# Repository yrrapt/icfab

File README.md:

# ICFab

Currently only includes a DMD based lithography protoype design.

The design has been created for use with the ZTurn Zynq development board for driving the information to the DMD chip.

The design is created in KiCad.
The BOM can be found here: [BOM](https://htmlpreview.github.io/?https://github.com/yrrapt/icfab/blob/master/Design/Projector/DLP_Board/dlp_01/dlp_01_sch_brd/bom/ibom.html)

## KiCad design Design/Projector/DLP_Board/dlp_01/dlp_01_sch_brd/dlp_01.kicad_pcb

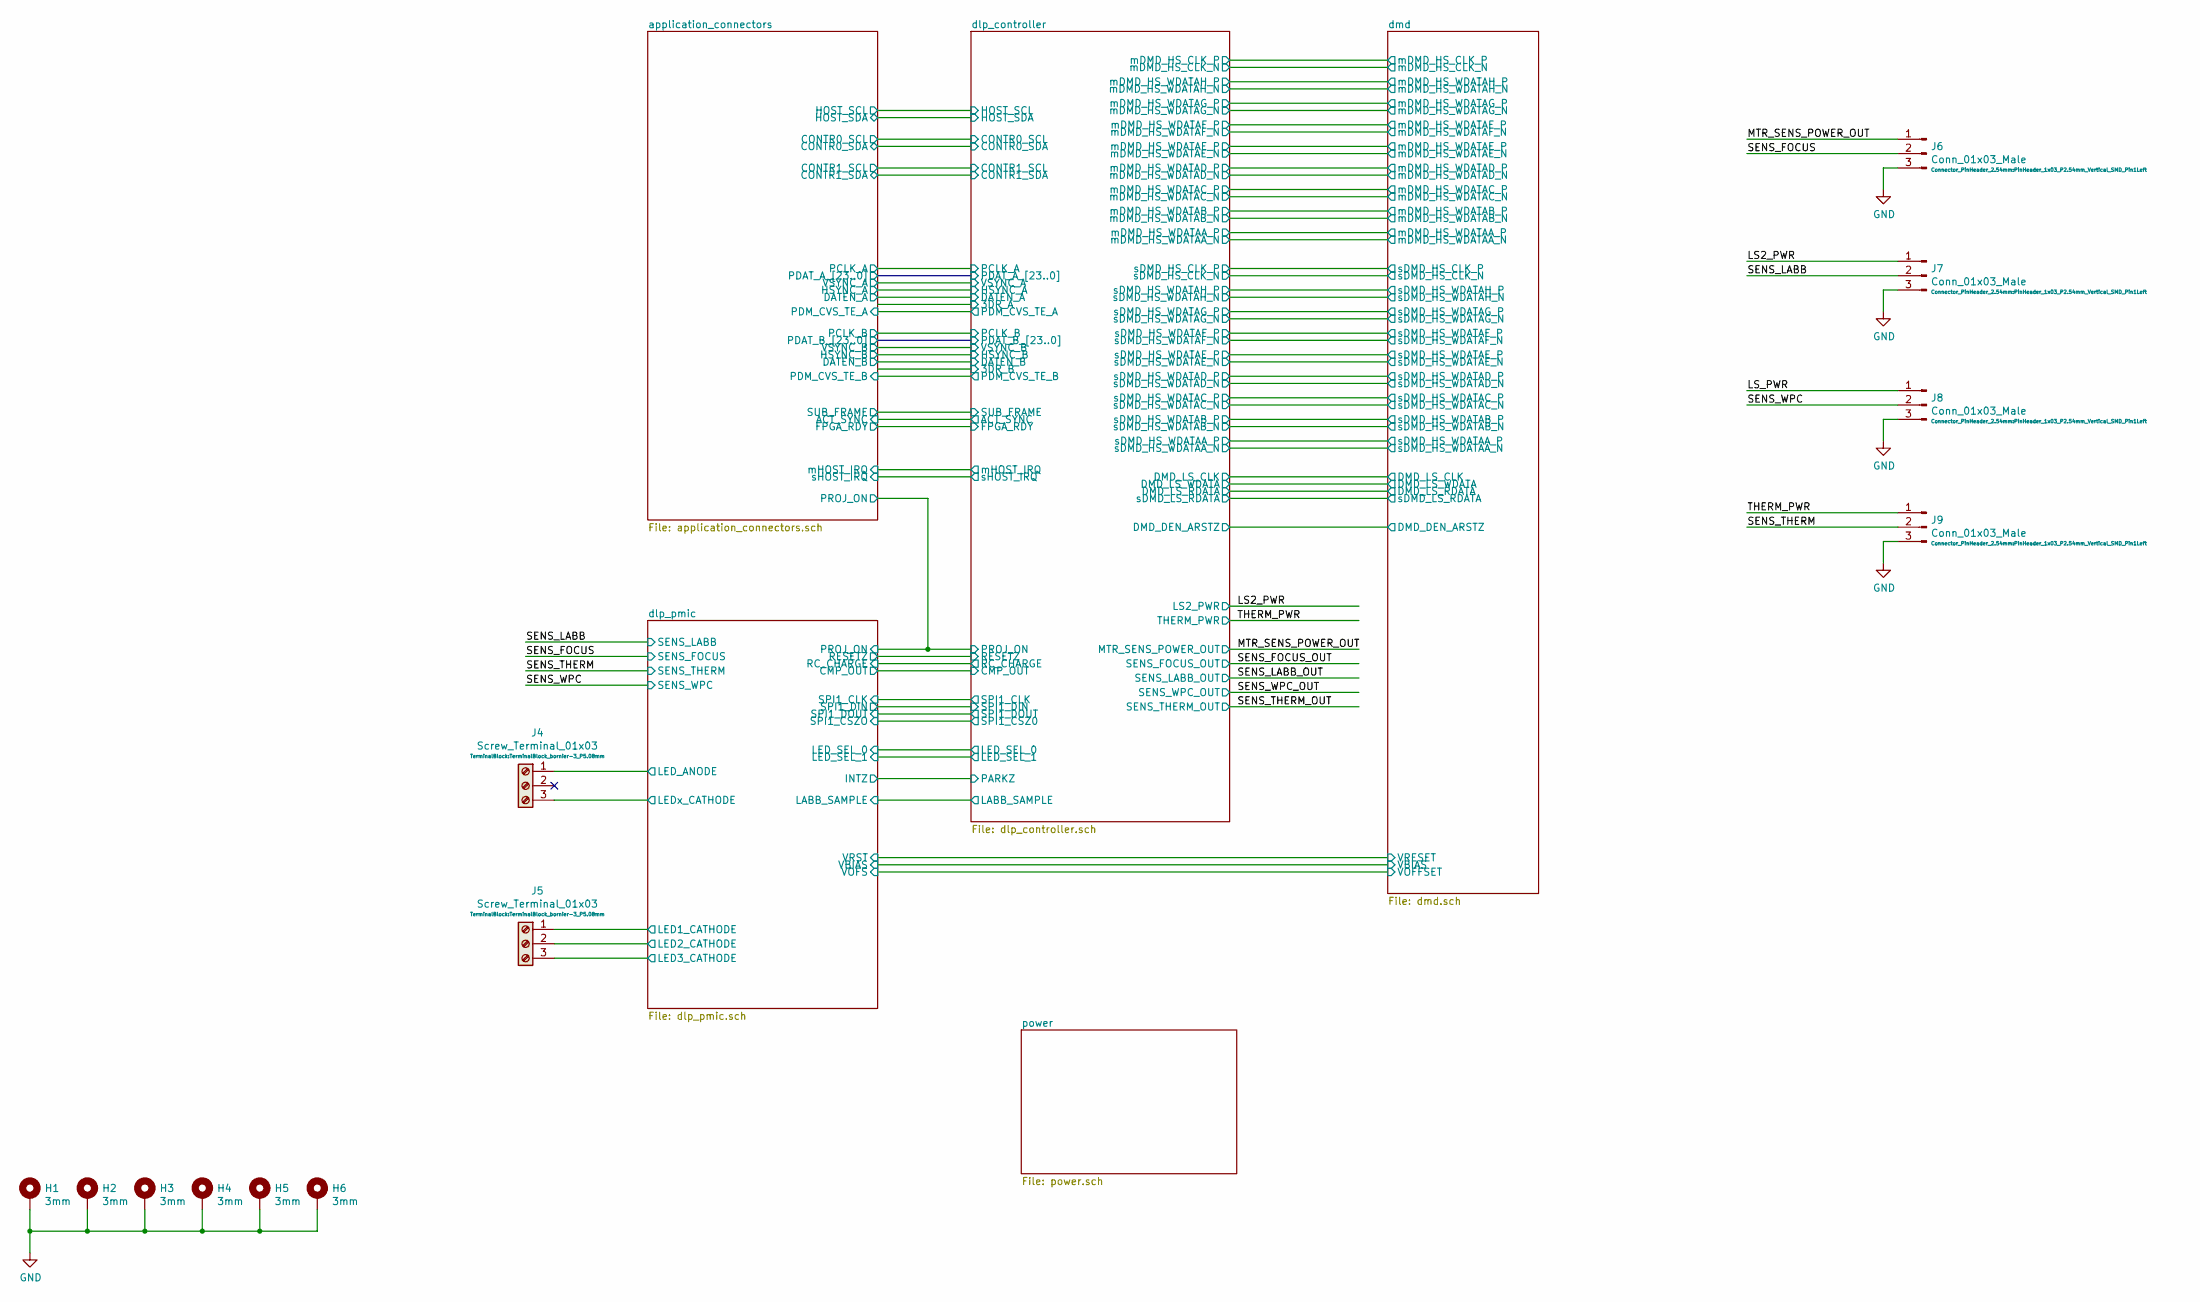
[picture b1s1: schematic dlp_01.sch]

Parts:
H1, H2, H3, H4, H5, H6: 3mm; MountingHole_3.2mm_M3_Pad_Via
J4, J5: Screw_Terminal_01x03; TerminalBlock_bornier-3_P5.08mm; part-num TB006-508-03BE
J6, J7, J8, J9: Conn_01x03_Male; PinHeader_1x03_P2.54mm_Vertical_SMD_Pin1Left; part-num 87898-0306

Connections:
/LS2_PWR: J7.1; also elsewhere on the board
/LS_PWR: J8.1
/MTR_SENS_POWER_OUT: J6.1; also elsewhere on the board
/SENS_FOCUS: J6.2; also elsewhere on the board
/SENS_LABB: J7.2; also elsewhere on the board
/SENS_THERM: J9.2; also elsewhere on the board
/SENS_WPC: J8.2; also elsewhere on the board
/THERM_PWR: J9.1; also elsewhere on the board
/dlp_pmic/LED1_CATHODE: J5.1; also elsewhere on the board
/dlp_pmic/LED2_CATHODE: J5.2; also elsewhere on the board
/dlp_pmic/LED3_CATHODE: J5.3; also elsewhere on the board
/dlp_pmic/LED_ANODE: J4.1; also elsewhere on the board
/dlp_pmic/LEDx_CATHODE: J4.3; also elsewhere on the board
GND: H1.1, H2.1, H3.1, H4.1, H5.1, H6.1, J6.3, J7.3, J8.3, J9.3; also elsewhere on the board

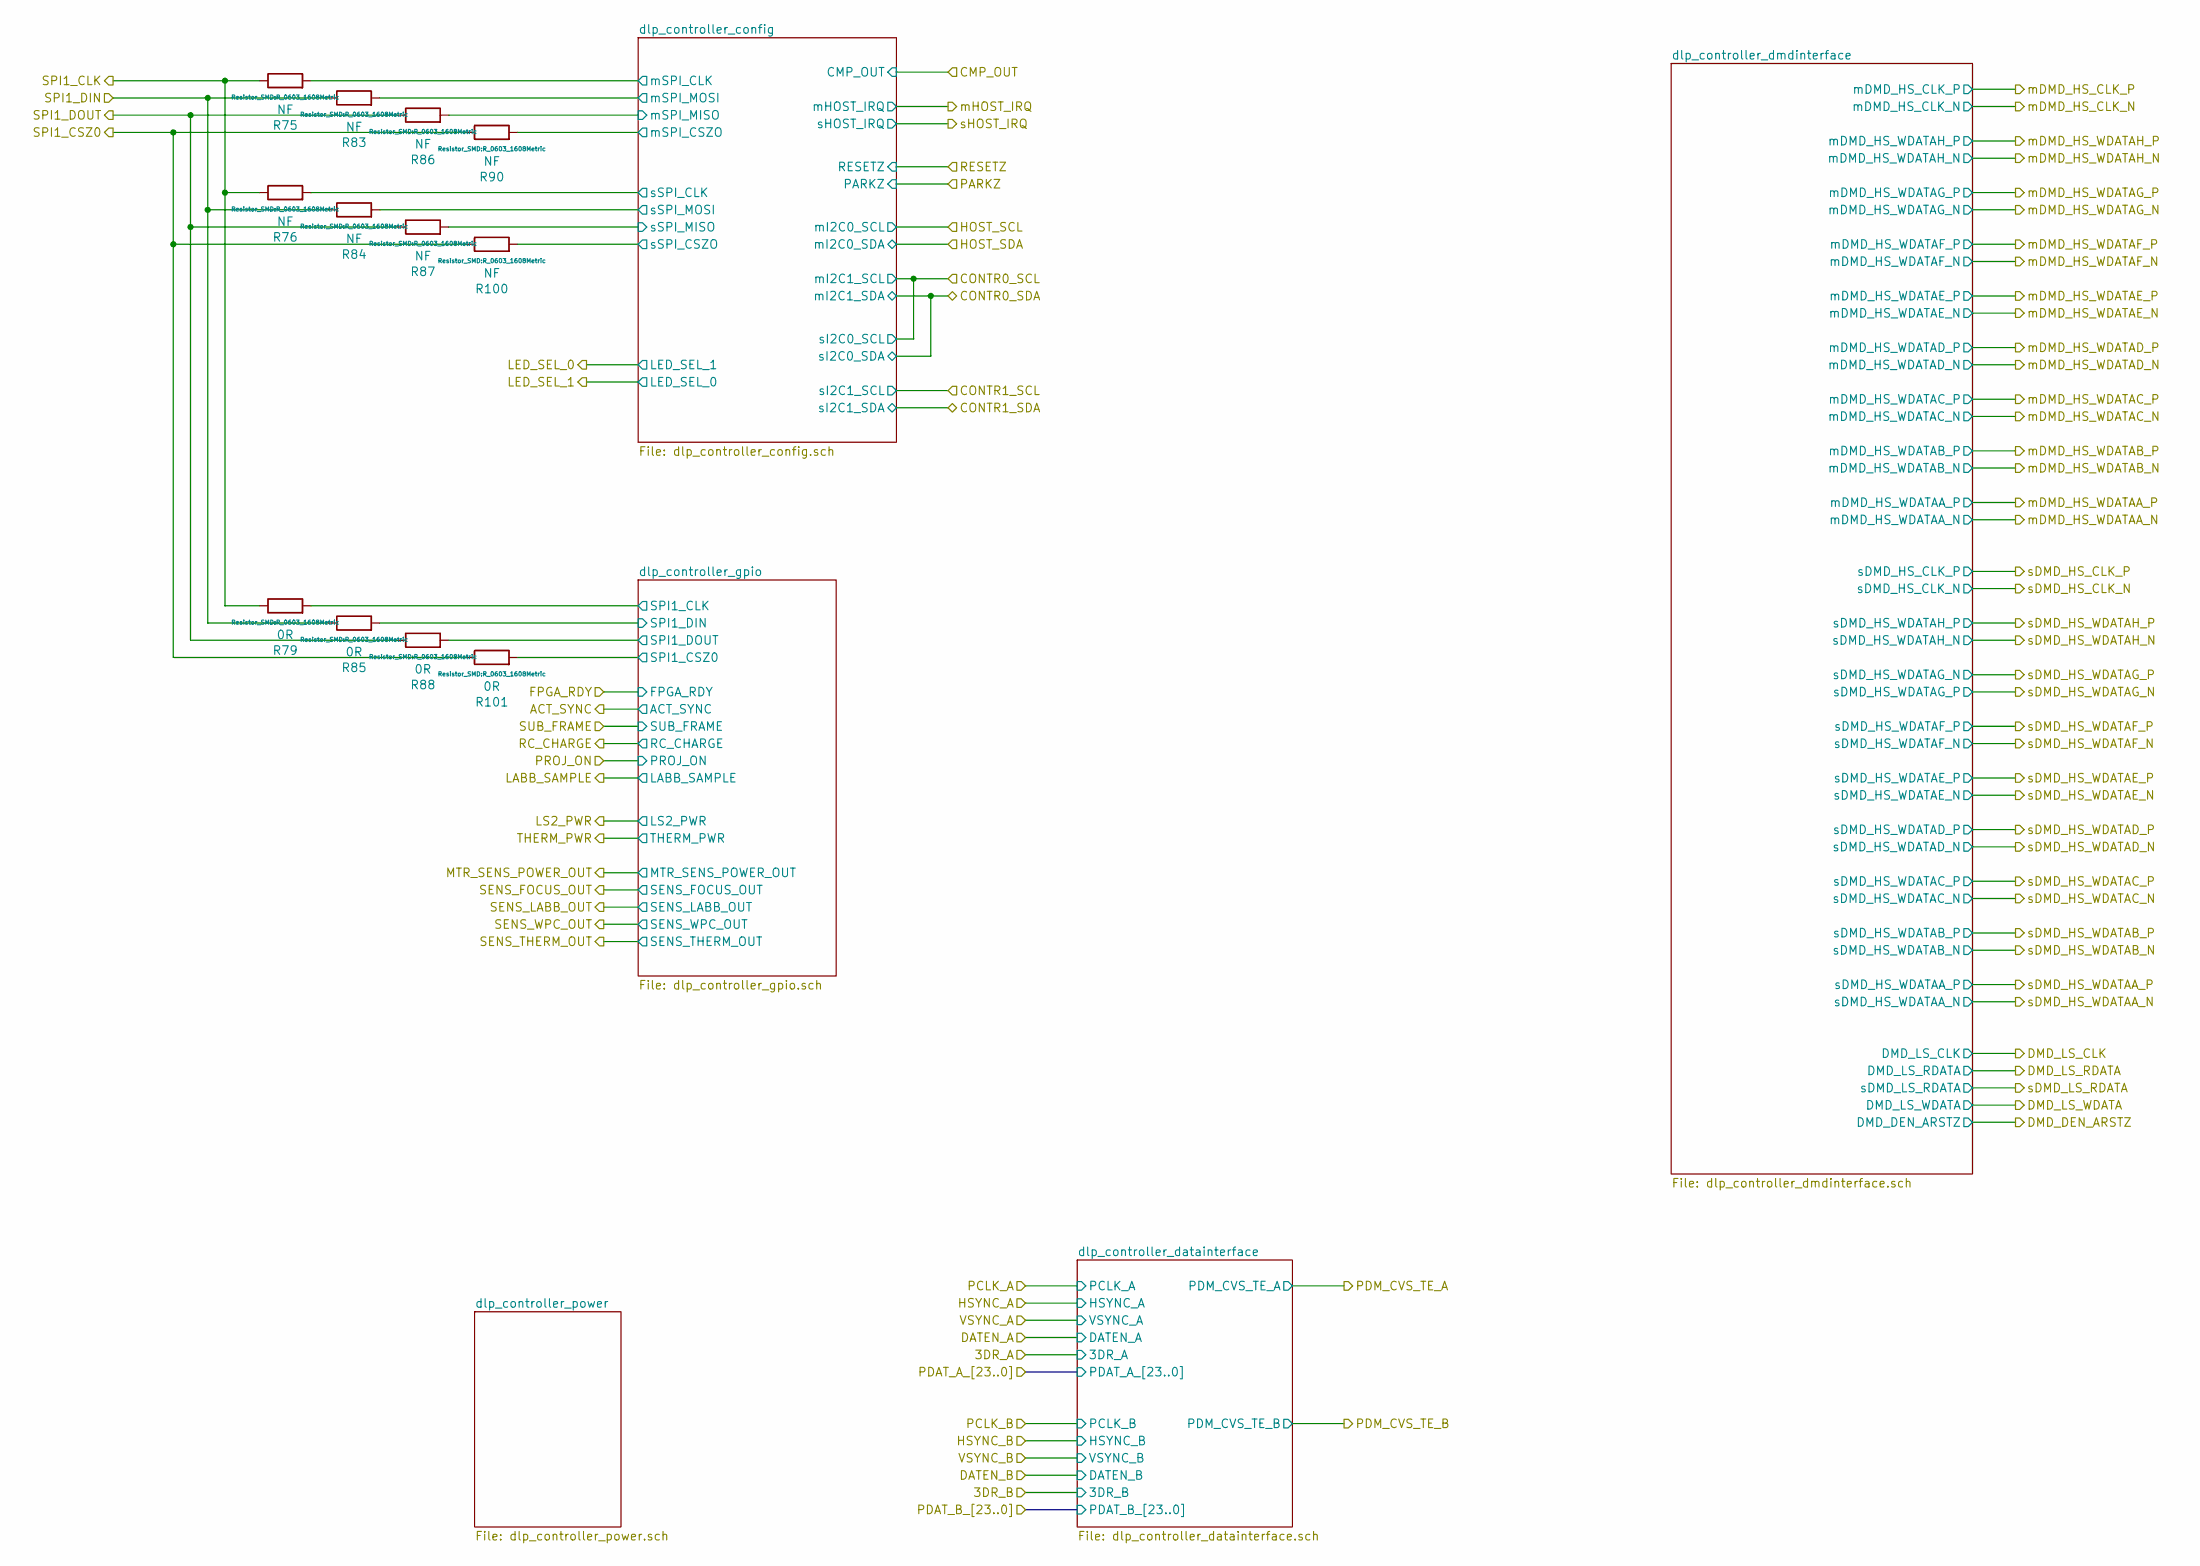
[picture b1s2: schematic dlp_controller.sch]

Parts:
R75, R76, R83, R84, R86, R87, R90, R100: NF; R_0603_1608Metric; part-num NF
R79, R85, R88, R101: 0R; R_0603_1608Metric; part-num CRCW06030000Z0EAC

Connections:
/dlp_controller/SPI1_CLK: R75.1, R76.1, R79.1; also elsewhere on the board
/dlp_controller/SPI1_CSZ0: R90.1, R100.1, R101.1; also elsewhere on the board
/dlp_controller/SPI1_DIN: R83.1, R84.1, R85.1; also elsewhere on the board
/dlp_controller/SPI1_DOUT: R86.1, R87.1, R88.1; also elsewhere on the board
/dlp_controller/dlp_controller_config/mSPI_CLK: R75.2; also elsewhere on the board
/dlp_controller/dlp_controller_config/mSPI_CSZO: R90.2; also elsewhere on the board
/dlp_controller/dlp_controller_config/mSPI_MISO: R86.2; also elsewhere on the board
/dlp_controller/dlp_controller_config/mSPI_MOSI: R83.2; also elsewhere on the board
/dlp_controller/dlp_controller_config/sSPI_CLK: R76.2; also elsewhere on the board
/dlp_controller/dlp_controller_config/sSPI_CSZO: R100.2; also elsewhere on the board
/dlp_controller/dlp_controller_config/sSPI_MISO: R87.2; also elsewhere on the board
/dlp_controller/dlp_controller_config/sSPI_MOSI: R84.2; also elsewhere on the board
/dlp_controller/dlp_controller_gpio/SPI1_CLK: R79.2; also elsewhere on the board
/dlp_controller/dlp_controller_gpio/SPI1_CSZ0: R101.2; also elsewhere on the board
/dlp_controller/dlp_controller_gpio/SPI1_DIN: R85.2; also elsewhere on the board
/dlp_controller/dlp_controller_gpio/SPI1_DOUT: R88.2; also elsewhere on the board

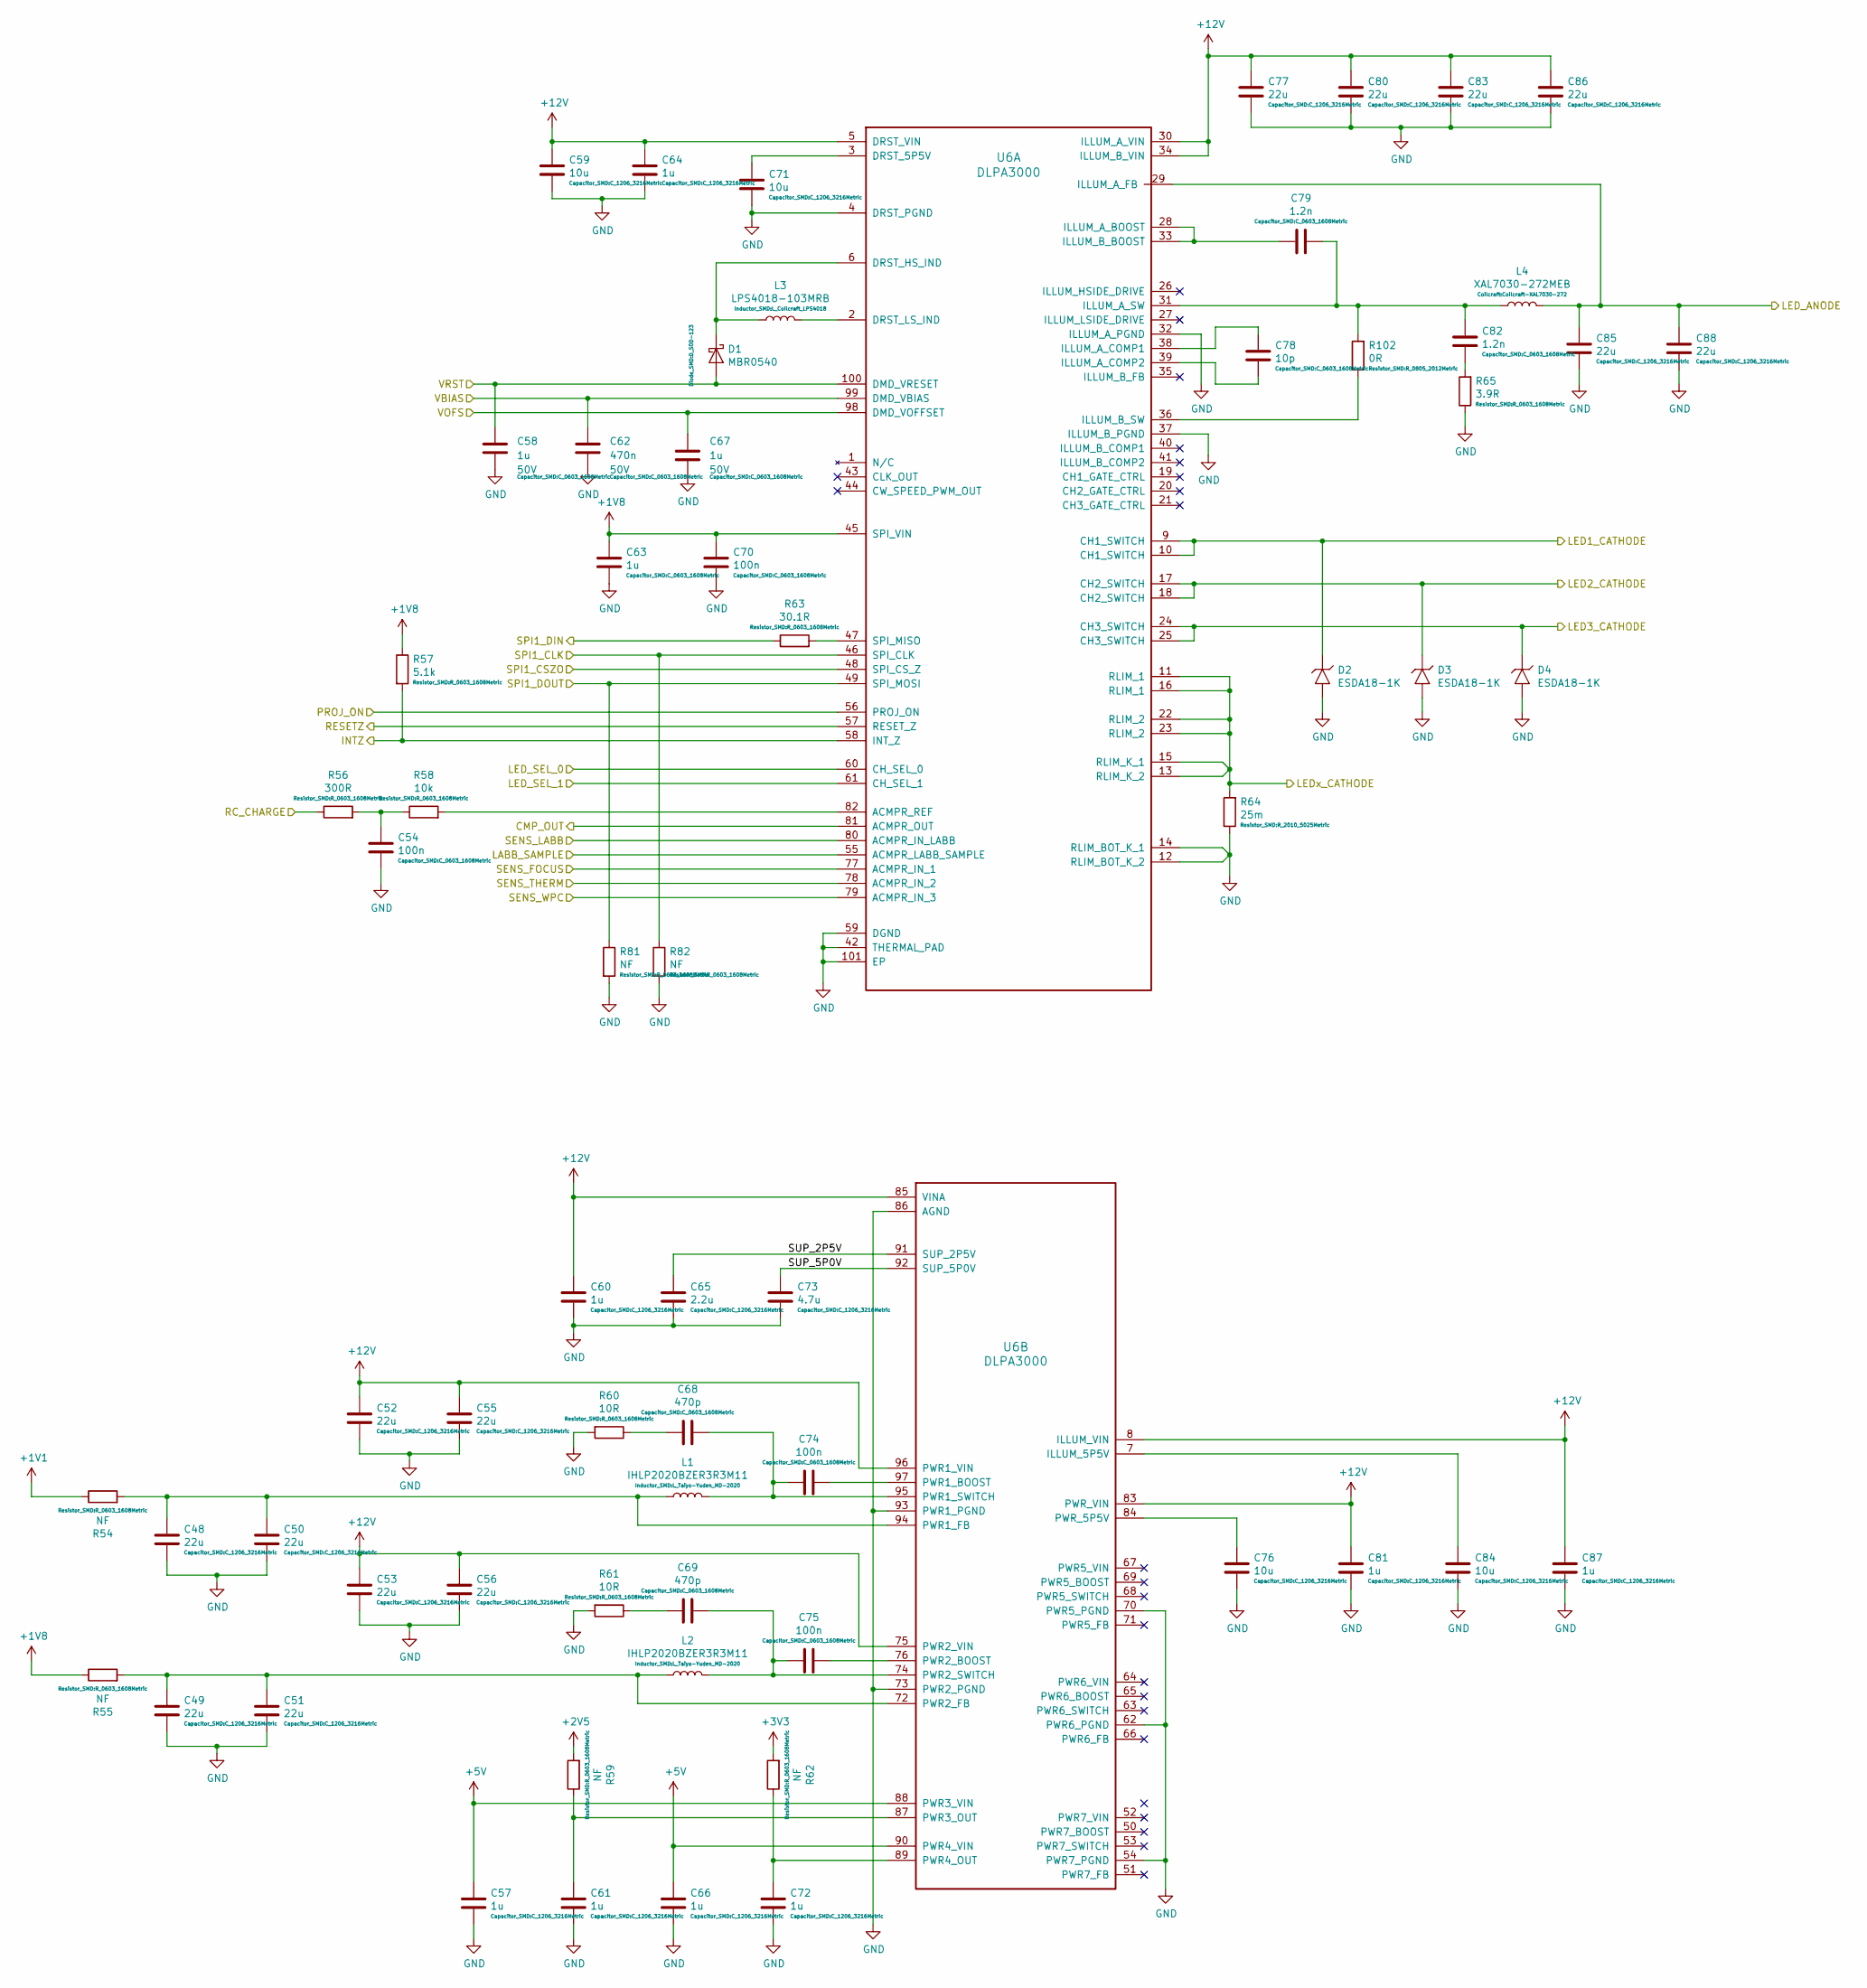
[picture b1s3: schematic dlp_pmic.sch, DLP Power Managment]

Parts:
C48, C49, C50, C51, C52, C53, C55, C56, C77, C80, C83, C85, C86, C88: 22u; C_1206_3216Metric; part-num 12063D226MAT2A
C54, C70, C74, C75: 100n; C_0603_1608Metric; part-num 06033C104KAT4A
C57, C60, C61, C64, C66, C72, C81, C87: 1u; C_1206_3216Metric; part-num 12065C105KAZ4A
C58, C67: 1u; C_0603_1608Metric; Voltage 50V; part-num GRT188R61H105KE13D
C59, C71, C76, C84: 10u; C_1206_3216Metric; part-num 12065D106KAT2A
C62: 470n; C_0603_1608Metric; Voltage 50V; part-num C1608X7R1H474K080AC
C63: 1u; C_0603_1608Metric; part-num GRT188R61H105KE13D
C65: 2.2u; C_1206_3216Metric; part-num 12065C225K4T2A
C68, C69: 470p; C_0603_1608Metric; part-num 06033C471KAT4A
C73: 4.7u; C_1206_3216Metric; part-num 12065C475KAT4A
C78: 10p; C_0603_1608Metric; part-num 06033C100KAT2A
C79, C82: 1.2n; C_0603_1608Metric; part-num 06033C122KAT2A
D1: MBR0540; D_SOD-123; part-num MBR0540
D2, D3, D4: ESDA18-1K; D_SOD-523; part-num ESDA18-1K
L1, L2: IHLP2020BZER3R3M11; L_Taiyo-Yuden_MD-2020; part-num IHLP2020BZER3R3M11
L3: LPS4018-103MRB; L_Coilcraft_LPS4018; part-num LPS4018-103MRB
L4: XAL7030-272MEB; Coilcraft-XAL7030-272; part-num XAL7030-272MEB
R54, R55, R59, R62, R81, R82: NF; R_0603_1608Metric; part-num NF
R56: 300R; R_0603_1608Metric; part-num CRCW0603300RFKEA
R57: 5.1k; R_0603_1608Metric; part-num CRCW06035K10FKEA
R58: 10k; R_0603_1608Metric; part-num CRCW060310K0FKEA
R60, R61: 10R; R_0603_1608Metric; part-num CRCW060310R0FKEA
R63: 30.1R; R_0603_1608Metric; part-num CRCW060330R1FKEA
R64: 25m; R_2010_5025Metric; part-num CRCW20100000Z0EF
R65: 3.9R; R_0603_1608Metric; part-num CRCW06033R90FKEA
R102: 0R; R_0805_2012Metric; part-num CRCW08050000Z0EAC
U6: DLPA3000; TQFP-100-1EP_14x14mm_P0.5mm_EP5x5mm; part-num DLPA3000DPFD

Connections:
+1V1: R54.1; also elsewhere on the board
+1V8: C63.2, C70.2, R55.1, R57.1, U6.45 (SPI_VIN); also elsewhere on the board
+2V5: R59.2
+5V: C57.2, C66.2, U6.88 (PWR3_VIN), U6.90 (PWR4_VIN); also elsewhere on the board
+12V: C52.2, C53.2, C55.2, C56.2, C59.2, C60.2, C64.2, C77.2, C80.2, C81.2, C83.2, C86.2, C87.2, U6.5 (DRST_VIN), U6.8 (ILLUM_VIN), U6.30 (ILLUM_A_VIN), U6.34 (ILLUM_B_VIN), U6.75 (PWR2_VIN), U6.83 (PWR_VIN), U6.85 (VINA), U6.96 (PWR1_VIN); also elsewhere on the board
/SENS_FOCUS: U6.77 (ACMPR_IN_1); also elsewhere on the board
/SENS_LABB: U6.80 (ACMPR_IN_LABB); also elsewhere on the board
/SENS_THERM: U6.78 (ACMPR_IN_2); also elsewhere on the board
/SENS_WPC: U6.79 (ACMPR_IN_3); also elsewhere on the board
/application_connectors/PROJ_ON: U6.56 (PROJ_ON); also elsewhere on the board
/dlp_controller/CMP_OUT: U6.81 (ACMPR_OUT); also elsewhere on the board
/dlp_controller/LABB_SAMPLE: U6.55 (ACMPR_LABB_SAMPLE); also elsewhere on the board
/dlp_controller/LED_SEL_0: U6.60 (CH_SEL_0); also elsewhere on the board
/dlp_controller/LED_SEL_1: U6.61 (CH_SEL_1); also elsewhere on the board
/dlp_controller/RC_CHARGE: R56.1; also elsewhere on the board
/dlp_controller/RESETZ: U6.57 (RESET_Z); also elsewhere on the board
/dlp_controller/SPI1_CLK: R82.1, U6.46 (SPI_CLK); also elsewhere on the board
/dlp_controller/SPI1_CSZ0: U6.48 (SPI_CS_Z); also elsewhere on the board
/dlp_controller/SPI1_DIN: R63.1; also elsewhere on the board
/dlp_controller/SPI1_DOUT: R81.1, U6.49 (SPI_MOSI); also elsewhere on the board
/dlp_pmic/INTZ: R57.2, U6.58 (INT_Z); also elsewhere on the board
/dlp_pmic/LED1_CATHODE: D2.1 (K), U6.9 (CH1_SWITCH), U6.10 (CH1_SWITCH); also elsewhere on the board
/dlp_pmic/LED2_CATHODE: D3.1 (K), U6.17 (CH2_SWITCH), U6.18 (CH2_SWITCH); also elsewhere on the board
/dlp_pmic/LED3_CATHODE: D4.1 (K), U6.24 (CH3_SWITCH), U6.25 (CH3_SWITCH); also elsewhere on the board
/dlp_pmic/LED_ANODE: C85.2, C88.2, L4.2, U6.29 (ILLUM_A_FB); also elsewhere on the board
/dlp_pmic/LEDx_CATHODE: R64.2, U6.11 (RLIM_1), U6.13 (RLIM_K_2), U6.15 (RLIM_K_1), U6.16 (RLIM_1), U6.22 (RLIM_2), U6.23 (RLIM_2); also elsewhere on the board
/dlp_pmic/SUP_2P5V: C65.2, U6.91 (SUP_2P5V)
/dlp_pmic/SUP_5P0V: C73.2, U6.92 (SUP_5P0V)
/dlp_pmic/VBIAS: C62.2, U6.99 (DMD_VBIAS); also elsewhere on the board
/dmd/VOFFSET: C67.2, U6.98 (DMD_VOFFSET); also elsewhere on the board
/dmd/VRESET: C58.2, D1.2 (A), U6.100 (DMD_VRESET); also elsewhere on the board
GND: C48.1, C49.1, C50.1, C51.1, C52.1, C53.1, C54.1, C55.1, C56.1, C57.1, C58.1, C59.1, C60.1, C61.1, C62.1, C63.1, C64.1, C65.1, C66.1, C67.1, C70.1, C71.1, C72.1, C73.1, C76.1, C77.1, C80.1, C81.1, C83.1, C84.1, C85.1, C86.1, C87.1, C88.1, D2.2 (A), D3.2 (A), D4.2 (A), R60.2, R61.2, R64.1, R65.1, R81.2, R82.2, U6.4 (DRST_PGND), U6.12 (RLIM_BOT_K_2), U6.14 (RLIM_BOT_K_1), U6.32 (ILLUM_A_PGND), U6.37 (ILLUM_B_PGND), U6.42 (THERMAL_PAD), U6.54 (PWR7_PGND), U6.59 (DGND), U6.62 (PWR6_PGND), U6.70 (PWR5_PGND), U6.73 (PWR2_PGND), U6.86 (AGND), U6.93 (PWR1_PGND), U6.101 (EP); also elsewhere on the board
unnamed: C48.2, C50.2, L1.1, R54.2, U6.94 (PWR1_FB)
unnamed: C49.2, C51.2, L2.1, R55.2, U6.72 (PWR2_FB)
unnamed: C54.2, R56.2, R58.1
unnamed: C61.2, R59.1, U6.87 (PWR3_OUT)
unnamed: C68.1, R60.1
unnamed: C68.2, C74.1, L1.2, U6.95 (PWR1_SWITCH)
unnamed: C69.1, R61.1
unnamed: C69.2, C75.1, L2.2, U6.74 (PWR2_SWITCH)
unnamed: C71.2, U6.3 (DRST_5P5V)
unnamed: C72.2, R62.1, U6.89 (PWR4_OUT)
unnamed: C74.2, U6.97 (PWR1_BOOST)
unnamed: C75.2, U6.76 (PWR2_BOOST)
unnamed: C76.2, U6.84 (PWR_5P5V)
unnamed: C78.1, U6.38 (ILLUM_A_COMP1)
unnamed: C78.2, U6.39 (ILLUM_A_COMP2)
unnamed: C79.1, U6.28 (ILLUM_A_BOOST), U6.33 (ILLUM_B_BOOST)
unnamed: C79.2, C82.2, L4.1, R102.2, U6.31 (ILLUM_A_SW)
unnamed: C82.1, R65.2
unnamed: C84.2, U6.7 (ILLUM_5P5V)
unnamed: D1.1 (K), L3.1, U6.6 (DRST_HS_IND)
unnamed: L3.2, U6.2 (DRST_LS_IND)
unnamed: R58.2, U6.82 (ACMPR_REF)
unnamed: R63.2, U6.47 (SPI_MISO)
unnamed: R102.1, U6.36 (ILLUM_B_SW)

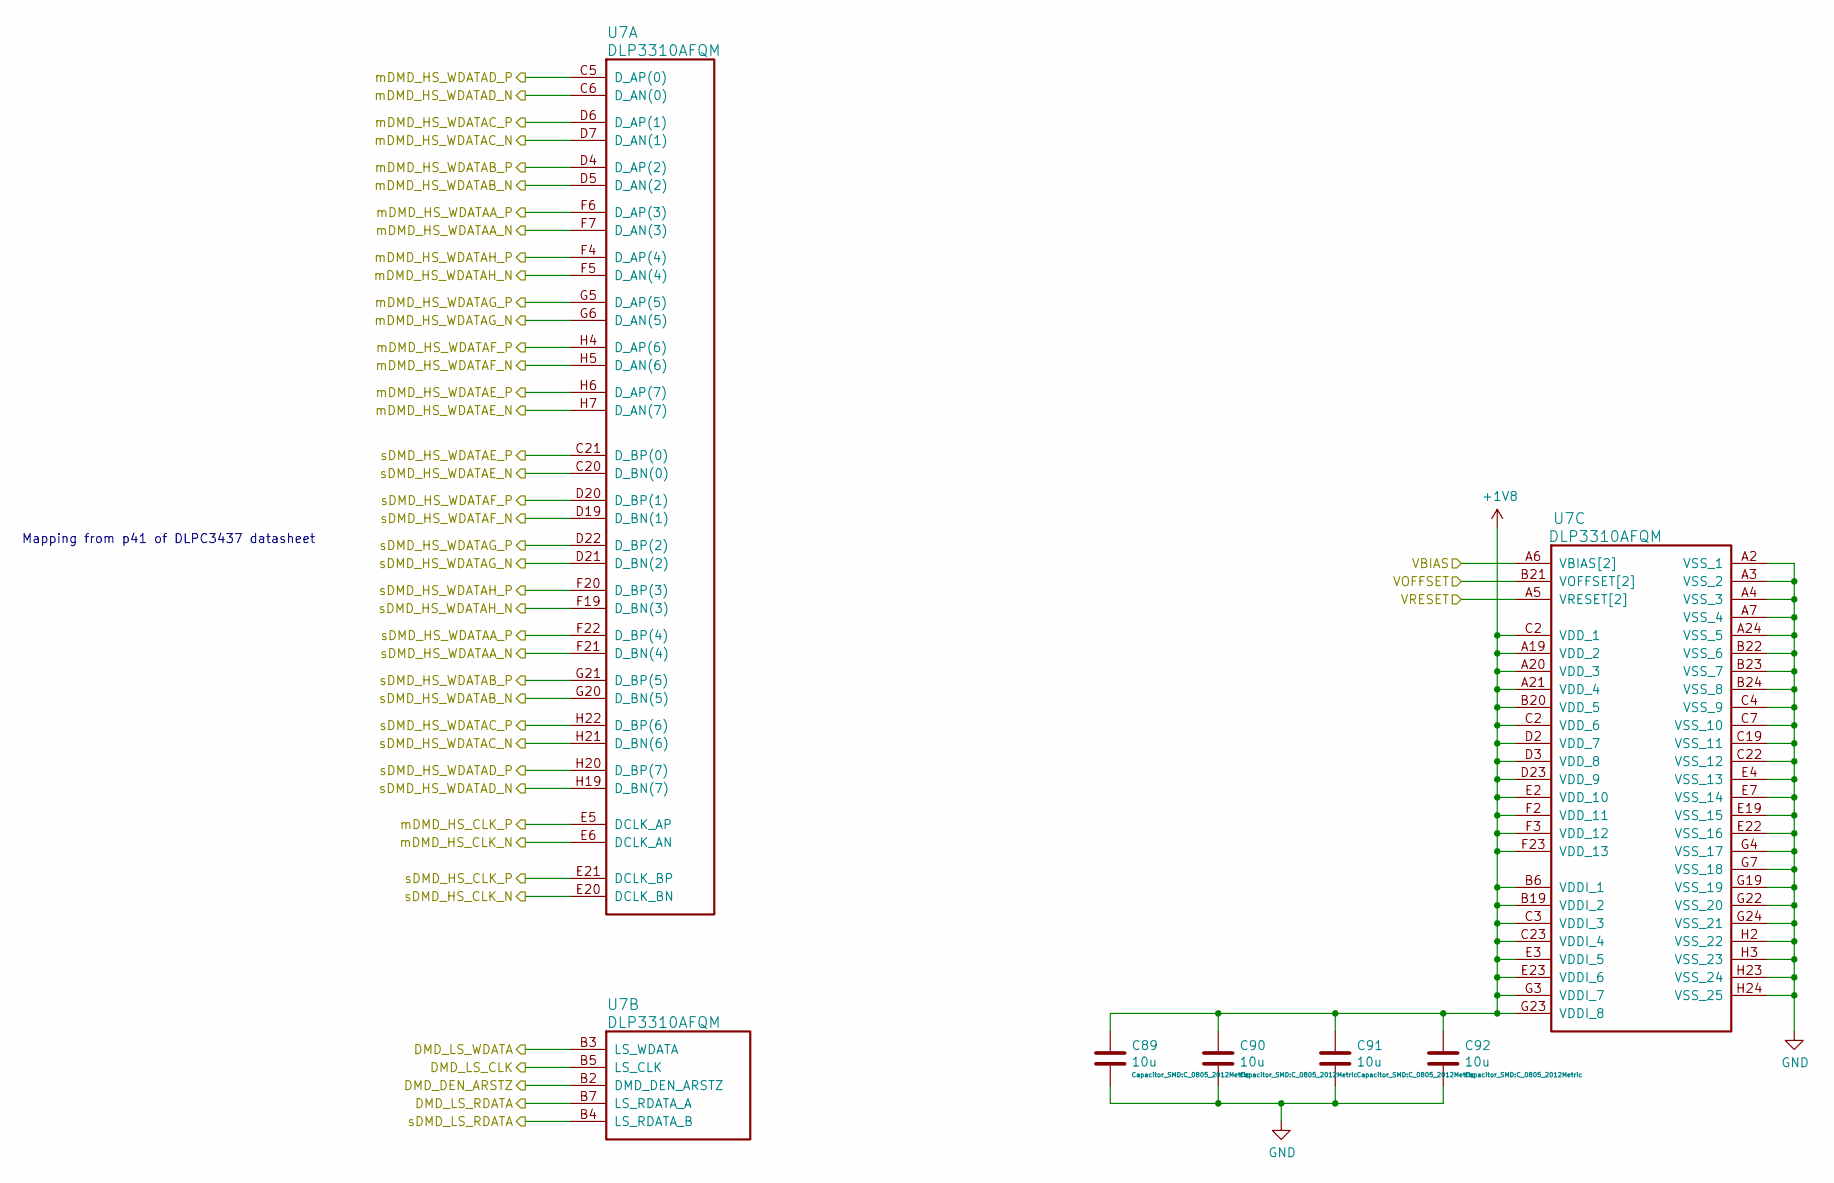
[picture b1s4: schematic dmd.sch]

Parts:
C89, C90, C91, C92: 10u; C_0805_2012Metric; part-num 0805ZC106KAT4A
U7: DLP3310AFQM; DLP3310; part-num DLP3310AFQM

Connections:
+1V8: C89.1, C90.1, C91.1, C92.1, U7.A19 (VDD_2), U7.A20 (VDD_3), U7.A21 (VDD_4), U7.B6 (VDDI_1), U7.B19 (VDDI_2), U7.B20 (VDD_5), U7.C2 (VDD_1), U7.C3 (VDDI_3), U7.C23 (VDDI_4), U7.D2 (VDD_7), U7.D3 (VDD_8), U7.D23 (VDD_9), U7.E2 (VDD_10), U7.E3 (VDDI_5), U7.E23 (VDDI_6), U7.F2 (VDD_11), U7.F3 (VDD_12), U7.F23 (VDD_13), U7.G3 (VDDI_7), U7.G23 (VDDI_8); also elsewhere on the board
/dlp_controller/DMD_DEN_ARSTZ: U7.B2 (DMD_DEN_ARSTZ); also elsewhere on the board
/dlp_controller/DMD_LS_CLK: U7.B5 (LS_CLK); also elsewhere on the board
/dlp_controller/DMD_LS_RDATA: U7.B7 (LS_RDATA_A); also elsewhere on the board
/dlp_controller/DMD_LS_WDATA: U7.B3 (LS_WDATA); also elsewhere on the board
/dlp_controller/mDMD_HS_CLK_N: U7.E6 (DCLK_AN); also elsewhere on the board
/dlp_controller/mDMD_HS_CLK_P: U7.E5 (DCLK_AP); also elsewhere on the board
/dlp_controller/mDMD_HS_WDATAA_N: U7.F7 (D_AN(3)); also elsewhere on the board
/dlp_controller/mDMD_HS_WDATAA_P: U7.F6 (D_AP(3)); also elsewhere on the board
/dlp_controller/mDMD_HS_WDATAB_N: U7.D5 (D_AN(2)); also elsewhere on the board
/dlp_controller/mDMD_HS_WDATAB_P: U7.D4 (D_AP(2)); also elsewhere on the board
/dlp_controller/mDMD_HS_WDATAC_N: U7.D7 (D_AN(1)); also elsewhere on the board
/dlp_controller/mDMD_HS_WDATAC_P: U7.D6 (D_AP(1)); also elsewhere on the board
/dlp_controller/mDMD_HS_WDATAD_N: U7.C6 (D_AN(0)); also elsewhere on the board
/dlp_controller/mDMD_HS_WDATAD_P: U7.C5 (D_AP(0)); also elsewhere on the board
/dlp_controller/mDMD_HS_WDATAE_N: U7.H7 (D_AN(7)); also elsewhere on the board
/dlp_controller/mDMD_HS_WDATAE_P: U7.H6 (D_AP(7)); also elsewhere on the board
/dlp_controller/mDMD_HS_WDATAF_N: U7.H5 (D_AN(6)); also elsewhere on the board
/dlp_controller/mDMD_HS_WDATAF_P: U7.H4 (D_AP(6)); also elsewhere on the board
/dlp_controller/mDMD_HS_WDATAG_N: U7.G6 (D_AN(5)); also elsewhere on the board
/dlp_controller/mDMD_HS_WDATAG_P: U7.G5 (D_AP(5)); also elsewhere on the board
/dlp_controller/mDMD_HS_WDATAH_N: U7.F5 (D_AN(4)); also elsewhere on the board
/dlp_controller/mDMD_HS_WDATAH_P: U7.F4 (D_AP(4)); also elsewhere on the board
/dlp_controller/sDMD_HS_CLK_N: U7.E20 (DCLK_BN); also elsewhere on the board
/dlp_controller/sDMD_HS_CLK_P: U7.E21 (DCLK_BP); also elsewhere on the board
/dlp_controller/sDMD_HS_WDATAA_N: U7.F21 (D_BN(4)); also elsewhere on the board
/dlp_controller/sDMD_HS_WDATAA_P: U7.F22 (D_BP(4)); also elsewhere on the board
/dlp_controller/sDMD_HS_WDATAB_N: U7.G20 (D_BN(5)); also elsewhere on the board
/dlp_controller/sDMD_HS_WDATAB_P: U7.G21 (D_BP(5)); also elsewhere on the board
/dlp_controller/sDMD_HS_WDATAC_N: U7.H21 (D_BN(6)); also elsewhere on the board
/dlp_controller/sDMD_HS_WDATAC_P: U7.H22 (D_BP(6)); also elsewhere on the board
/dlp_controller/sDMD_HS_WDATAD_N: U7.H19 (D_BN(7)); also elsewhere on the board
/dlp_controller/sDMD_HS_WDATAD_P: U7.H20 (D_BP(7)); also elsewhere on the board
/dlp_controller/sDMD_HS_WDATAE_N: U7.C20 (D_BN(0)); also elsewhere on the board
/dlp_controller/sDMD_HS_WDATAE_P: U7.C21 (D_BP(0)); also elsewhere on the board
/dlp_controller/sDMD_HS_WDATAF_N: U7.D19 (D_BN(1)); also elsewhere on the board
/dlp_controller/sDMD_HS_WDATAF_P: U7.D20 (D_BP(1)); also elsewhere on the board
/dlp_controller/sDMD_HS_WDATAG_N: U7.D21 (D_BN(2)); also elsewhere on the board
/dlp_controller/sDMD_HS_WDATAG_P: U7.D22 (D_BP(2)); also elsewhere on the board
/dlp_controller/sDMD_HS_WDATAH_N: U7.F19 (D_BN(3)); also elsewhere on the board
/dlp_controller/sDMD_HS_WDATAH_P: U7.F20 (D_BP(3)); also elsewhere on the board
/dlp_controller/sDMD_LS_RDATA: U7.B4 (LS_RDATA_B); also elsewhere on the board
/dlp_pmic/VBIAS: U7.A6 (VBIAS[2]), U7.A22 (VBIAS[2]); also elsewhere on the board
/dmd/VOFFSET: U7.B21 (VOFFSET[2]), U7.G2 (VOFFSET[2]); also elsewhere on the board
/dmd/VRESET: U7.A5 (VRESET[2]), U7.A23 (VRESET[2]); also elsewhere on the board
GND: C89.2, C90.2, C91.2, C92.2, U7.A2 (VSS_1), U7.A3 (VSS_2), U7.A4 (VSS_3), U7.A7 (VSS_4), U7.A24 (VSS_5), U7.B22 (VSS_6), U7.B23 (VSS_7), U7.B24 (VSS_8), U7.C4 (VSS_9), U7.C7 (VSS_10), U7.C19 (VSS_11), U7.C22 (VSS_12), U7.E4 (VSS_13), U7.E7 (VSS_14), U7.E19 (VSS_15), U7.E22 (VSS_16), U7.G4 (VSS_17), U7.G7 (VSS_18), U7.G19 (VSS_19), U7.G22 (VSS_20), U7.G24 (VSS_21), U7.H2 (VSS_22), U7.H3 (VSS_23), U7.H23 (VSS_24), U7.H24 (VSS_25); also elsewhere on the board

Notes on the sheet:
Mapping from p41 of DLPC3437 datasheet
